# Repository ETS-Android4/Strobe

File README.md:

# Strobe
Repository contains Arduino program and Android application used for one of my physics projects in high school. The project was a device to show stroboscopic effect on a stream of water.
Embedded (Arduino) program controls the operation of the device like colors of RGB LEDs, electromagnet, water pump. Android app provides easy to use interface to remote change parameters (frequency, colors etc.) in realtime by bluetooth.

## Android app
| Home | Palette |
| - | - |
|  |  |

##### Android app tested only on Xiaomi mi A1

## Example of effects
| | | | |
|-|-|-| - |
| |  |  |  |

## Board

|||
|-|-|
|  | |

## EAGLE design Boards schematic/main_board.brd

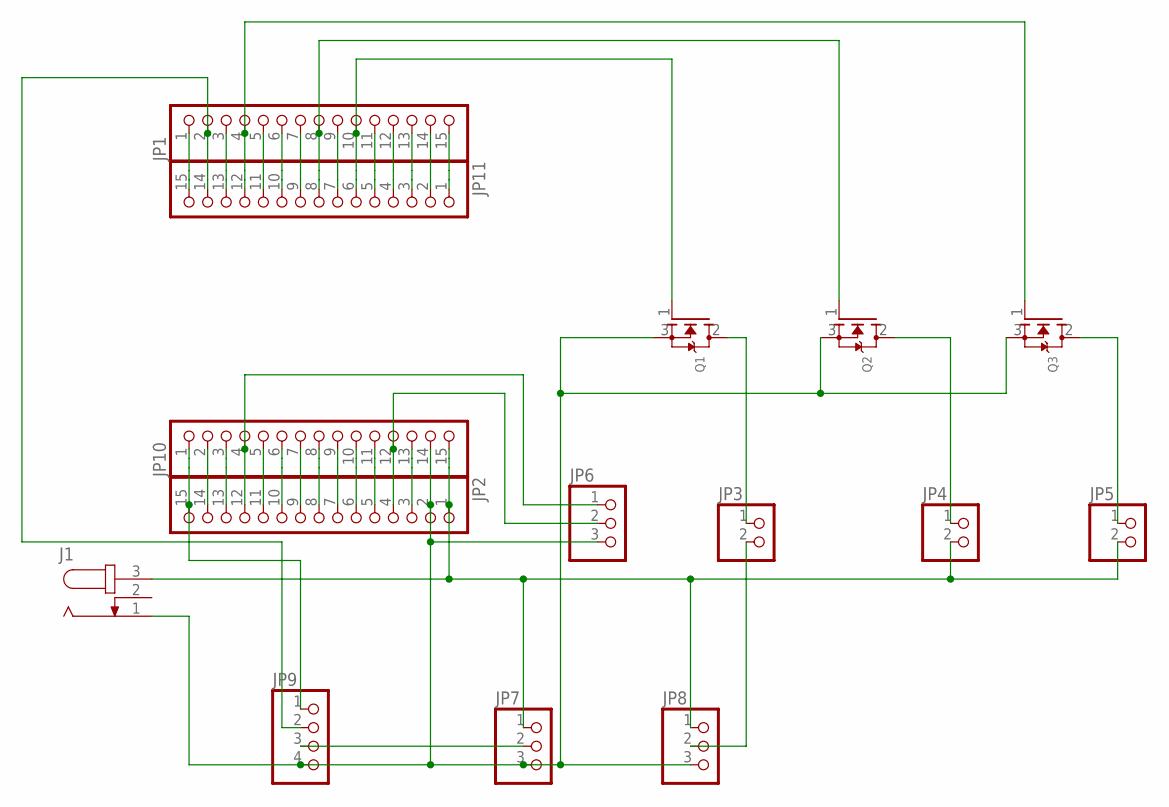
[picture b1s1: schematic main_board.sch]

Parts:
J1: JACK-PLUG1; SPC4078
JP1, JP2, JP10, JP11: PINHD-1X15; 1X15
JP3, JP4, JP5: PINHD-1X2; 1X02
JP6, JP7, JP8: PINHD-1X3; 1X03
JP9: PINHD-1X4; 1X04
Q1, Q2, Q3: MOSFET-NGDS_TO220V; TO220V

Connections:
unnamed: JP2.15, JP9.1, JP10.1
unnamed: JP2.14, JP10.2
unnamed: JP2.13, JP10.3
unnamed: JP2.12, JP6.1, JP10.4
unnamed: JP2.11, JP10.5
unnamed: JP2.10, JP10.6
unnamed: JP2.9, JP10.7
unnamed: JP2.8, JP10.8
unnamed: JP2.7, JP10.9
unnamed: JP2.6, JP10.10
unnamed: JP2.5, JP10.11
unnamed: JP2.4, JP6.2, JP10.12
unnamed: JP2.3, JP10.13
unnamed: J1.1, JP2.2, JP6.3, JP7.3, JP8.3, JP9.4, JP10.14, Q1.3 (S), Q2.3 (S), Q3.3 (S)
unnamed: J1.3, JP2.1, JP4.2, JP5.2, JP7.1, JP8.1, JP10.15
unnamed: JP1.15, JP11.1
unnamed: JP1.14, JP11.2
unnamed: JP1.13, JP11.3
unnamed: JP1.12, JP11.4
unnamed: JP1.11, JP11.5
unnamed: JP1.10, JP11.6, Q1.1 (G)
unnamed: JP1.9, JP11.7
unnamed: JP1.8, JP11.8, Q2.1 (G)
unnamed: JP1.7, JP11.9
unnamed: JP1.6, JP11.10
unnamed: JP1.5, JP11.11
unnamed: JP1.4, JP11.12, Q3.1 (G)
unnamed: JP1.3, JP11.13
unnamed: JP1.2, JP9.2, JP11.14
unnamed: JP1.1, JP11.15
unnamed: JP3.1, Q1.2 (D)
unnamed: JP4.1, Q2.2 (D)
unnamed: JP5.1, Q3.2 (D)
unnamed: JP3.2, JP8.2
unnamed: JP7.2, JP9.3

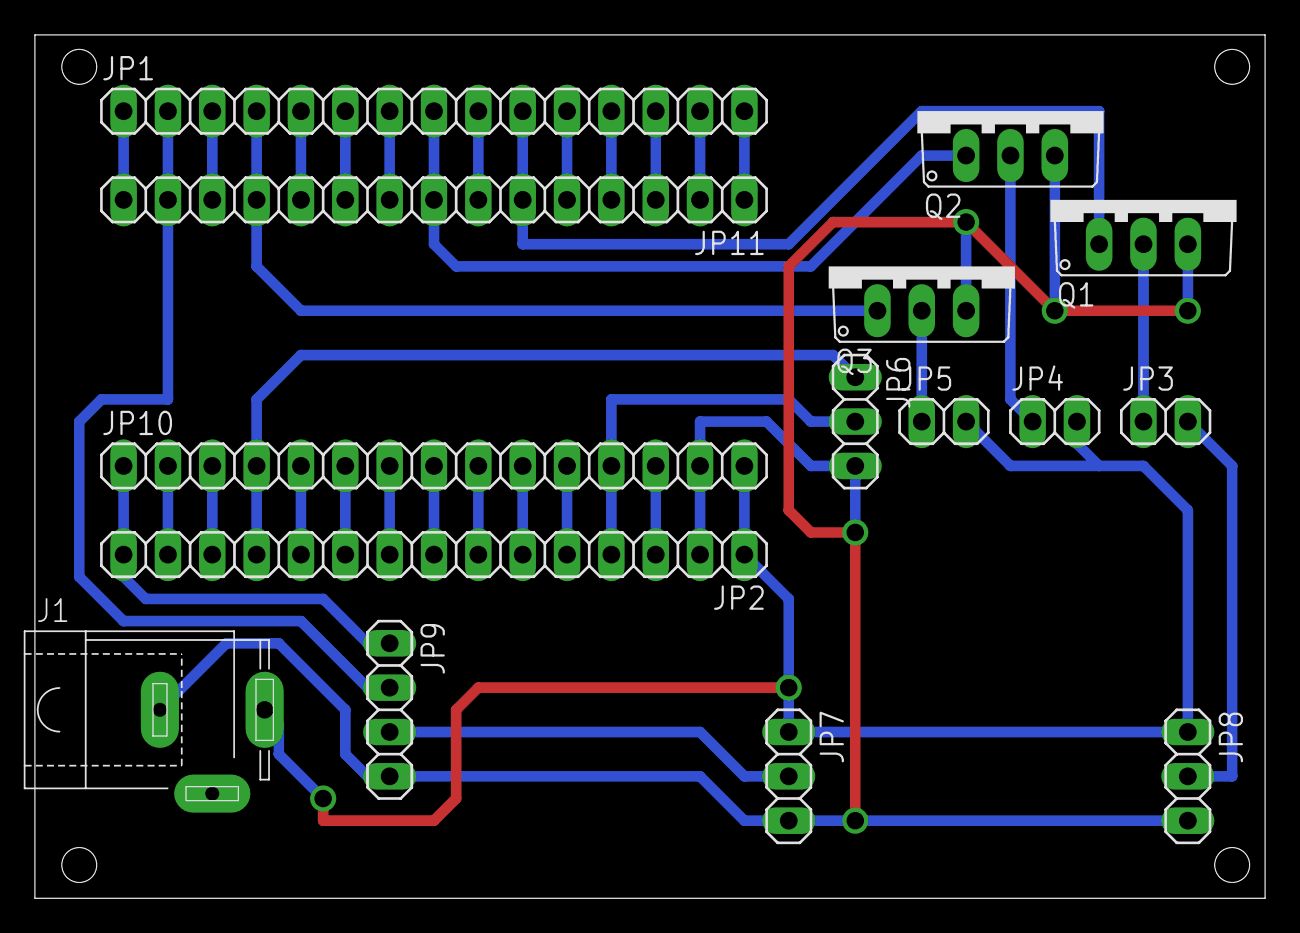
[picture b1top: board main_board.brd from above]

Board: 2 copper layers, 70.5 x 49.5 mm, 15 parts (0 on the bottom side), 35 nets.

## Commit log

2021-11-06 Upload boards schematics and arduino ino
2021-11-08 Android app upload
2021-11-08 images upload
2021-11-08 README update
2021-11-08 image fix
2022-02-18 Add more images and gifs to README
2022-02-18 Image size fix
2022-05-29 Push SonarCloud config file.
